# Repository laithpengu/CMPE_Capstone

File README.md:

# Repository for CMPE Capstone group ICS-Processor
## Contributors
- Ethan Swain (leader)
- Nick Battista
- Cole Cavanaugh
- Seth Ellis
- John Hair
## Contents
### CODE
- **controllerArduino**: Code for the arduino going on the controller
- **hdl**: All hdl code for each fpga
- **mem_files**: coefficient files that will be used for onbaord memory
- **dpi**: C code toward testing the control logic design with the other modules
### controllerKiCad: 
Schematics for the controller
### docs: 
Documentation of overall project information
### ICS_legacy: 
Legacy code from previous years

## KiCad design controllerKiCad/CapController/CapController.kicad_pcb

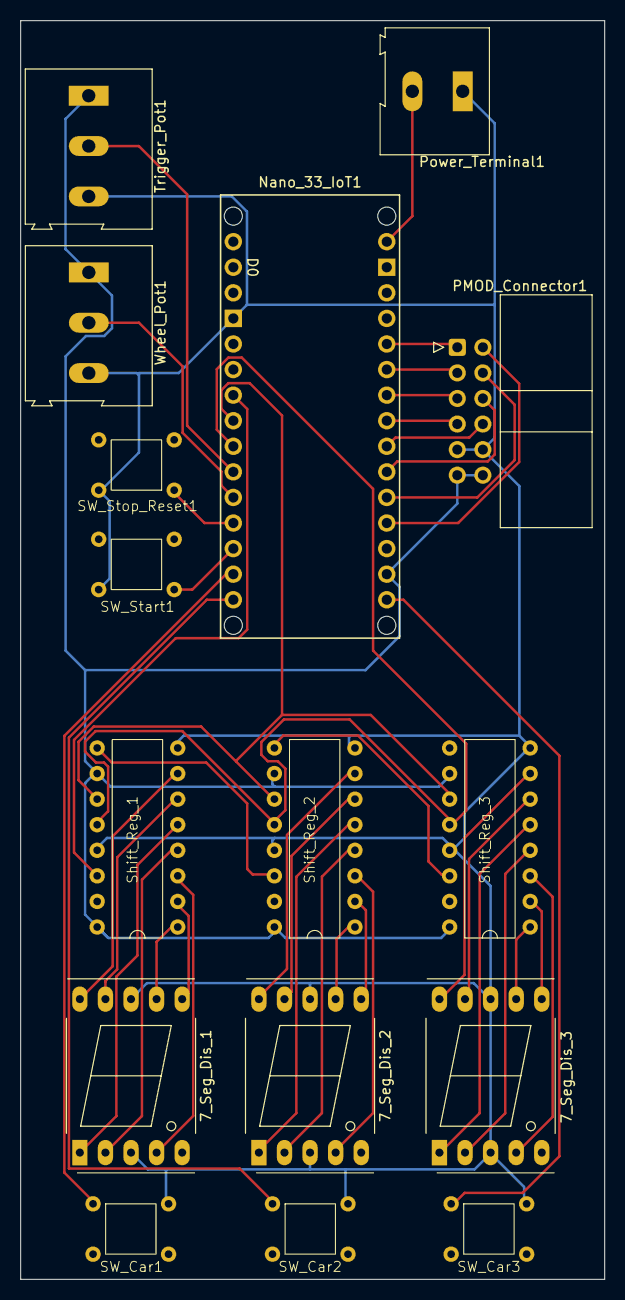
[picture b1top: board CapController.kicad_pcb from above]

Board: 2 copper layers, 58.0 x 125.0 mm, 16 parts (0 on the bottom side), 44 nets.

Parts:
7_Seg_Dis_1, 7_Seg_Dis_2, 7_Seg_Dis_3: LTS-6960HR; 7SegmentLED_LTS6760_LTS6780
Nano_33_IoT1: Arduino_Nano_33_IoT_Socket
PMOD_Connector1: Conn_02x06_Counter_Clockwise; IDC-Header_2x06_P2.54mm_Horizontal
Power_Terminal1: Screw_1x2; TerminalBlock_Altech_AK300-2_P5.00mm
SW_Car1, SW_Car2, SW_Car3: SW_MEC_5E; 4Pin_Button
SW_Start1: SW_MEC_5E; 4Pin_Button
SW_Stop_Reset1: SW_MEC_5E; 4Pin_Button
Shift_Reg_1, Shift_Reg_2, Shift_Reg_3: 74LS595; 74HC595_16Pin_DIP
Trigger_Pot1: Screw_1x3; TerminalBlock_Altech_AK300-3_P5.00mm
Wheel_Pot1: Screw_1x3; TerminalBlock_Altech_AK300-3_P5.00mm

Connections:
+5V: Nano_33_IoT1.3V3 (3.3V), PMOD_Connector1.11, PMOD_Connector1.12, Shift_Reg_1.10 (~SRCLR), Shift_Reg_1.16 (VCC), Shift_Reg_2.10 (~SRCLR), Shift_Reg_2.16 (VCC), Shift_Reg_3.10 (~SRCLR), Shift_Reg_3.16 (VCC), Trigger_Pot1.1, Wheel_Pot1.1
/LED_Data_In: Nano_33_IoT1.D4, Shift_Reg_1.14 (SER)
/LED_Data_In_CLK: Nano_33_IoT1.D5, Shift_Reg_1.11 (SRCLK), Shift_Reg_2.11 (SRCLK), Shift_Reg_3.11 (SRCLK)
/LED_Store_CLK: Nano_33_IoT1.D6, Shift_Reg_1.12 (RCLK), Shift_Reg_2.12 (RCLK), Shift_Reg_3.12 (RCLK)
GND: 7_Seg_Dis_1.3 (C.A.), 7_Seg_Dis_1.8 (C.A.), 7_Seg_Dis_2.3 (C.A.), 7_Seg_Dis_2.8 (C.A.), 7_Seg_Dis_3.3 (C.A.), 7_Seg_Dis_3.8 (C.A.), Nano_33_IoT1.GND1 (GND), PMOD_Connector1.9, PMOD_Connector1.10, Power_Terminal1.1, SW_Car1.4 (A), SW_Car2.4 (A), SW_Car3.4 (A), SW_Start1.4 (A), SW_Stop_Reset1.4 (A), Shift_Reg_1.8 (GND), Shift_Reg_1.13 (~OE), Shift_Reg_2.8 (GND), Shift_Reg_2.13 (~OE), Shift_Reg_3.8 (GND), Shift_Reg_3.13 (~OE), Trigger_Pot1.3, Wheel_Pot1.3
unnamed: 7_Seg_Dis_1.7 (a), Shift_Reg_1.1 (QB)
unnamed: 7_Seg_Dis_1.6 (b), Shift_Reg_1.2 (QC)
unnamed: 7_Seg_Dis_1.4 (c), Shift_Reg_1.3 (QD)
unnamed: 7_Seg_Dis_1.2 (d), Shift_Reg_1.4 (QE)
unnamed: 7_Seg_Dis_1.1 (e), Shift_Reg_1.5 (QF)
unnamed: 7_Seg_Dis_1.9 (f), Shift_Reg_1.6 (QG)
unnamed: 7_Seg_Dis_1.10 (g), Shift_Reg_1.7 (QH)
unnamed: 7_Seg_Dis_2.7 (a), Shift_Reg_2.1 (QB)
unnamed: 7_Seg_Dis_2.6 (b), Shift_Reg_2.2 (QC)
unnamed: 7_Seg_Dis_2.4 (c), Shift_Reg_2.3 (QD)
unnamed: 7_Seg_Dis_2.2 (d), Shift_Reg_2.4 (QE)
unnamed: 7_Seg_Dis_2.1 (e), Shift_Reg_2.5 (QF)
unnamed: 7_Seg_Dis_2.9 (f), Shift_Reg_2.6 (QG)
unnamed: 7_Seg_Dis_2.10 (g), Shift_Reg_2.7 (QH)
unnamed: 7_Seg_Dis_3.7 (a), Shift_Reg_3.1 (QB)
unnamed: 7_Seg_Dis_3.6 (b), Shift_Reg_3.2 (QC)
unnamed: 7_Seg_Dis_3.4 (c), Shift_Reg_3.3 (QD)
unnamed: 7_Seg_Dis_3.2 (d), Shift_Reg_3.4 (QE)
unnamed: 7_Seg_Dis_3.1 (e), Shift_Reg_3.5 (QF)
unnamed: 7_Seg_Dis_3.9 (f), Shift_Reg_3.6 (QG)
unnamed: 7_Seg_Dis_3.10 (g), Shift_Reg_3.7 (QH)
unnamed: Nano_33_IoT1.A0 (A0/DAC), PMOD_Connector1.2
unnamed: Nano_33_IoT1.A4 (A4/SDA), PMOD_Connector1.7
unnamed: Nano_33_IoT1.A5 (A5/SCL), PMOD_Connector1.5
unnamed: Nano_33_IoT1.D11 (D11_MOSI), SW_Car1.1
unnamed: Nano_33_IoT1.D12 (D12_MISO), SW_Car2.1
unnamed: Nano_33_IoT1.D13 (D13_SCK), SW_Car3.1
unnamed: Nano_33_IoT1.D9, SW_Stop_Reset1.1
unnamed: Nano_33_IoT1.D10, SW_Start1.1
unnamed: Nano_33_IoT1.A7, PMOD_Connector1.1
unnamed: Nano_33_IoT1.A6, PMOD_Connector1.3
unnamed: Nano_33_IoT1.A1, PMOD_Connector1.4
unnamed: Nano_33_IoT1.A2, PMOD_Connector1.6
unnamed: Nano_33_IoT1.A3, PMOD_Connector1.8
unnamed: Nano_33_IoT1.VIN, Power_Terminal1.2
unnamed: Shift_Reg_1.9 (QH'), Shift_Reg_2.14 (SER)
unnamed: Shift_Reg_2.9 (QH'), Shift_Reg_3.14 (SER)
unnamed: Nano_33_IoT1.D7, Trigger_Pot1.2
unnamed: Nano_33_IoT1.D8, Wheel_Pot1.2

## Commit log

2023-09-01 Created Readme file and docs directory
2023-09-01 test
2023-09-02 added legacy material
2023-09-06 added avoid code
2023-09-11 Wrote quick notes on the demo presentations
2023-09-11 notes on legacy code
2023-09-12 Started HTML Markdown File
    MD file still needs a lot more notes added to it, but main gist of basic level communication is documented
2023-09-13 Updated HTML docs
    better understand flow of network function, but communication between HTML and cars is still fuzzy other than the fact that they "use websockets"
2023-09-13 avoidance writeup
2023-10-17 greated pwm_gen
2023-10-17 cleanup
2023-10-20 fixed up pwm_gen and created a motor and servo control block
2023-10-21 Pushing first pass at SERDES
2023-10-25 Buffer started
    FIFO buffer started, testbench started as well
2023-10-27 pushing pc module, need to test and make coe file still
2023-10-28 Finished testing pc and made initial register file
    Still need to test the register file and make any changes
2023-10-28 FIFO tested
    FIFO testbench written, need to test more specific cases (how fast to read after writing, etc.) But FIFO logic works and is understood better.
2023-10-29 buffer comments added
    need to use john's SERDES but changes are being made to that, so current implementation in buffer is both wrong and commented out
2023-10-30 controller kicad files
2023-10-30 pushing regfile changes and start of testbench
2023-10-30 Almost done with SERDES testbench
2023-10-30 git ignore and controller code start
2023-10-30 moved arduino code
2023-11-13 standup meeting 3 gooning edition
2023-11-14 Regfile and serdes done
    Only problem with the serdes is idk how to properly test the serializer.
2023-11-15 pushing fixes to serdes
2023-11-18 Pushing fixes to register file and serdes with documentation on written modules
2023-11-20 Cleaned up file structure for hdl files
2023-11-22 Added RF Module
    Added RF control logic for testing
2023-11-22 test for RF
2023-11-26 standup doc thanksgiving edition
2023-11-27 cleaned up buffer file structure
2023-11-27 RF changes - S.Ellis
    *Pass the interrupt through the RF block
    *Pass the SDO from transceiver through the RF block
2023-11-29 Think UART is done
2023-12-01 Master file for FPGA
2023-12-01 coe + test
2023-12-04 demo test for John Hair - S. Ellis
2023-12-04 updates for demo test
2023-12-05 backup
2023-12-08 rf fix gyatttt
2023-12-10 Pushing finished packet display and updated pc instructions
2023-12-13 i am the best in the group
2023-12-14 Pushing RF changes
2023-12-16 pushing new pkt_display
2023-12-16 Pushing additions to the source folder
2023-12-18 to seth - "i love you" <3
2023-12-18 PWM Test files
2023-12-18 pushing pkt_display
2023-12-22 pushing some changes
2024-01-26 pushing new format for modules with regfile example
2024-01-26 pushing constraint file
2024-01-26 Before New Semester
    Pushing demo changes from the end of the fall semester to clean up local branch
2024-01-26 pushing newly formatted projects
2024-01-26 started synthesis scripting
2024-01-29 Cleaned up alot of the directories as well as fully written the uart controller
2024-01-31 standup 5: willy that wonka
    standup 5 and DPI stuff started
2024-01-31 Arduino Updates
2024-02-02 Pushing temp working UART controller and implementation
2024-02-02 Pushing final better version of UART controller
2024-02-04 Controller PCB Update
2024-02-04 Cleaned up UART to make it ready for use
    Cleaned up UART stuff, making a new module that combines the controller with the uart module and added documentation
2024-02-04 Cleaned up documentation
2024-02-05 Directory Cleanup
    Removed PWM_test, not needed
2024-02-05 Basic PWM setup
2024-02-05 pushing dpi files
    bunch of trash files are getting pushed too until I figure out how to gitignore them the best way
2024-02-06 added some mods to pwm
2024-02-07 finished controller and added legacy veh code
2024-02-07 RF Read test
    Added project for rf read testing
2024-02-08 fixed pwm speed
2024-02-08 tweaks and shit
2024-02-09 pwm update
2024-02-09 fixed some issues
2024-02-12 fifo updates
2024-02-14 PWM Fixes
    Fixed pwm clock divs and wrapper
2024-02-14 rf read test
2024-02-14 Updated new Buffer, TB needs work
    Second FIFO added, SERDES removed, all wires created and connected.
2024-02-14 arduino rf driver
    cloned arduino rf driver
2024-02-14 Testbench updated
2024-02-16 Pushing notes and start of tcling pwm
2024-02-16 rf read test updates w/ testbench
2024-02-16 new buffer naming scheme
2024-02-16 PWM works!!!!
2024-02-16 added arduino code
    added arduino transmit code
2024-02-19 Updated buffer signals
    Still need to do more error checking and check for read/write simultaneously
2024-02-19 FIFOs work in parallel
2024-02-19 buffer2.0 works, adding minor checks
2024-02-19 pushing pwm changes
2024-02-19 rf read updates
    includes updates to RF.sv, RF_cl_test.sv and RF read project
2024-02-20 rf read test updates
    Got the RF read function to work and output
2024-02-21 buffer's ALIVE
    Second iteration functioning properly, testbench works fully. Wrapper needs to be written
2024-02-21 rf read test updates
    Fixed latches, got simulation working and passed on board test with uart. Will test it with rf pmod on Friday.
2024-02-23 updates to rf read
2024-02-23 rf read updates
2024-02-23 rf read updates
    RF Read can read from the pmod
2024-02-23 Wrote test vehicle wrapper for avoidance
2024-02-24 pushing documentation
2024-02-25 Stand up 6 notes
2024-02-26 Last minute stand-up updates
    I made the changes last night just forgot to push.
2024-02-26 updated controller kicad files
2024-02-26 stand up presented
2024-02-26 Updates to rf_read
    Ethan wanted to see something in sim so mild changes were made
2024-02-29 pushing pwm fixes
2024-02-29 start of pkt_handler
2024-02-29 pushing written pkt_handler
2024-03-01 buffer md finished
2024-03-01 pushing updated and fixed pkt_handler
2024-03-01 Update RF_cl_test.sv
    For John
2024-03-01 pushing shit and stuff
2024-03-01 pkt handler uses 64 bits
    switched pkt handler to use a 64 bit packet
2024-03-01 pushing leader test
2024-03-04 Adding rf_working
2024-03-04 Got proc wrapper with receive working
2024-03-08 Create procTest.sv
    Added TB
2024-03-11 Pushing RF fixes (kinda)
2024-03-13 readded serdes!!!!!!1
    serdes added back because Avoidance can't use Microblaze
2024-03-14 pushing modified pkt_handler
2024-03-14 pushing fifo changes
2024-03-14 pushing last changes
2024-03-18 for seth transmit
2024-03-21 controller kicad updates
2024-03-21 downloaded software spi
2024-03-21 controller arduino update
    cleaned up old code and moved code from laptop to repo
2024-03-21 controller main start
    starting controller main code
2024-03-22 created pc wrapper for ila test
2024-03-25 pushing current changes
2024-03-29 started backup arduino code
2024-04-05 pwm working, renaming folder
2024-04-05 PWM working!
    Speed and Angle both working properly
2024-04-07 combined PWM with wifi code
2024-04-08 pushing standup 7 notes
2024-04-08 update to proc made send and recive functions
2024-04-10 pushing what I been having
2024-04-10 proto AT commander
2024-04-10 creating init procedure
2024-04-12 uart tx works for init commands
2024-04-12 rx for esp32
2024-04-17 rx ctrl
2024-04-19 pushing current bug fixes
2024-04-19 fasdfasjfsf
2024-04-21 pushing some esp changes
2024-04-22 pushing current working UART_TX and UART_RX
2024-04-22 cleaning some folders out
2024-04-24 pushing start
2024-04-24 pushing proc changes
2024-04-24 pushing send changes
2024-04-24 added controller setup
2024-04-24 fully uncommented controller arduino
2024-04-26 prototype vehicle selection code written
2024-04-27 pushing code with soft kill switch and code for follower vehicle when that test comes
2024-04-29 fixed up some syntax errors
2024-04-29 fixed uart interface for the monitor
2024-05-03 pushing current esp32 changes
2024-05-03 pushing with avoidance code
2024-05-03 added avoidance's setup function
2024-05-03 pushing no avoidance version
2024-05-03 controller wifi updates
2024-05-03 pushing broken seal
2024-05-04 pushing integrated avoidance code (doesn't work yet)
2024-05-04 pushing cleanup of repo
2024-05-04 pushing AP test
2024-05-10 pushing changes
2024-05-10 pushing changes to speed up messages
2024-05-10 code for vehicle 3
2024-05-10 UDP WORKING
2024-05-11 Added working vehicle selection
2024-05-15 controller update
2024-05-17 pushing current proc
2024-05-17 pushing new basic avoidance
2024-05-20 final updates
    final UDP updates
